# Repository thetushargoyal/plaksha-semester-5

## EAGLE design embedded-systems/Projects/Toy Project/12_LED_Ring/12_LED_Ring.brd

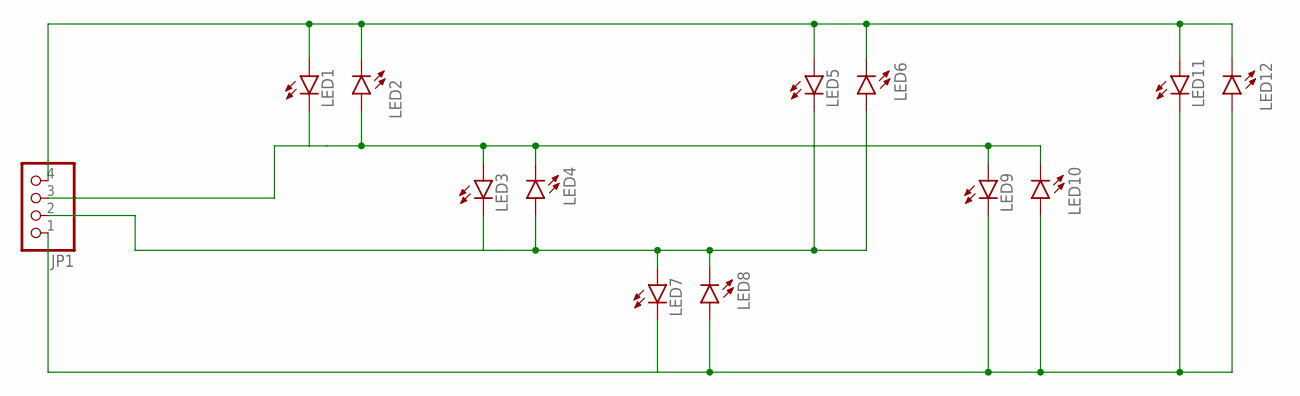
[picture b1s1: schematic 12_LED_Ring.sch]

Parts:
JP1: PINHD-1X4; 1X04
LED1, LED2, LED3, LED4, LED5, LED6, LED7, LED8, LED9, LED10, LED11, LED12: LED5MM

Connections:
unnamed: JP1.4, LED1.A, LED2.K (C), LED5.A, LED6.K (C), LED11.A, LED12.K (C)
unnamed: JP1.3, LED1.K (C), LED2.A, LED3.A, LED4.K (C), LED9.A, LED10.K (C)
unnamed: JP1.2, LED3.K (C), LED4.A, LED5.K (C), LED6.A, LED7.A, LED8.K (C)
unnamed: JP1.1, LED7.K (C), LED8.A, LED9.K (C), LED10.A, LED11.K (C), LED12.A

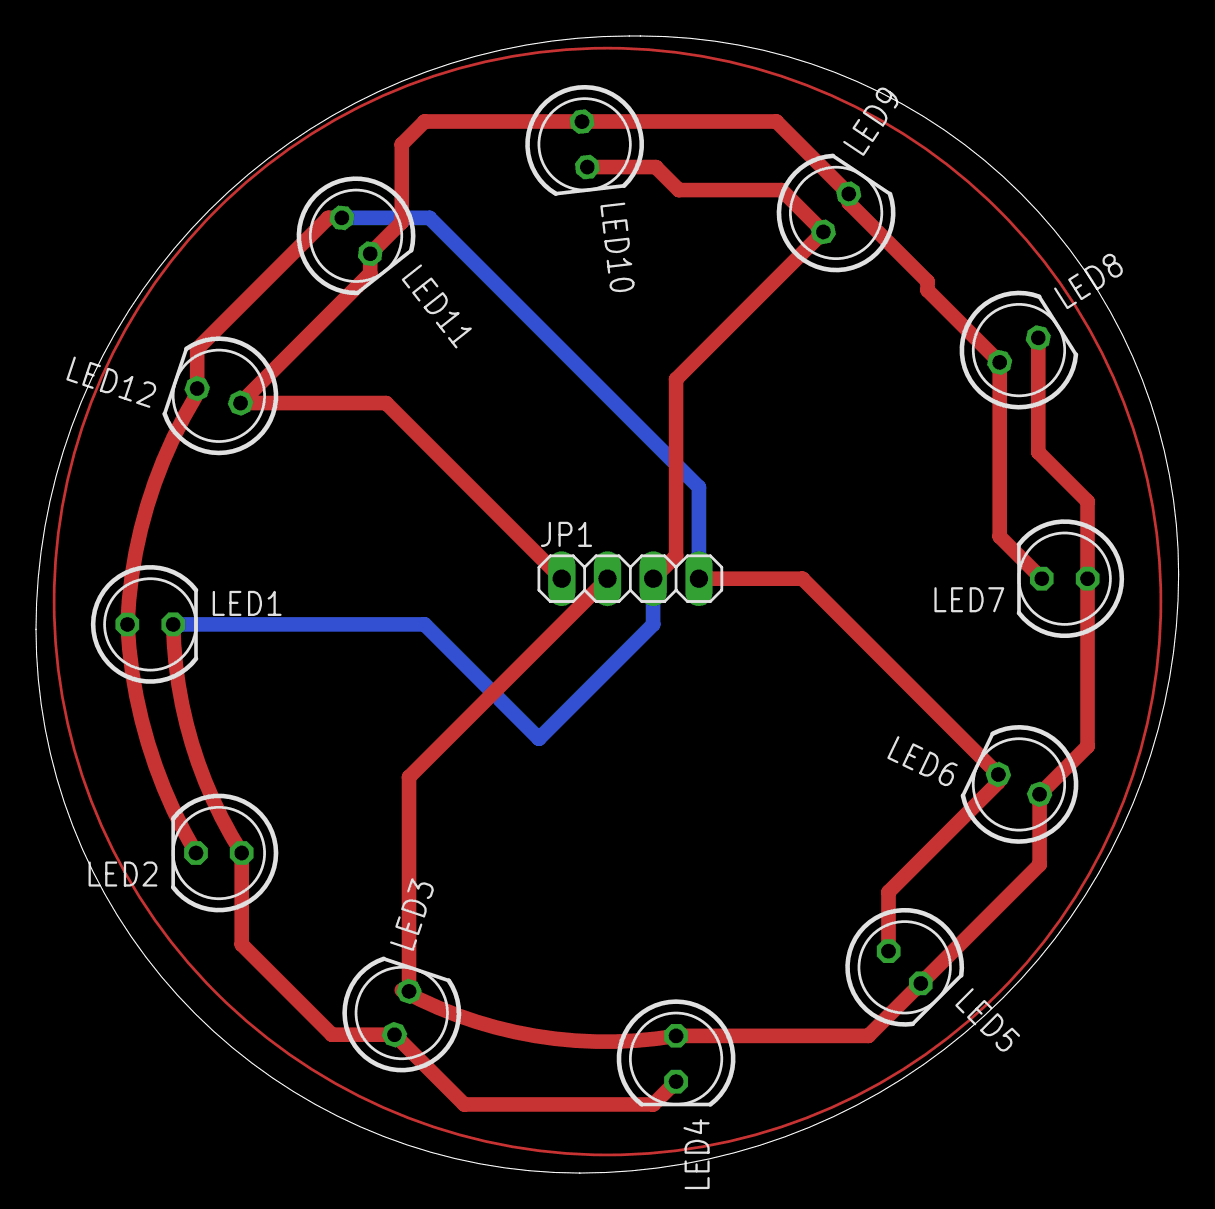
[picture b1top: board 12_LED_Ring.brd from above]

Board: 2 copper layers, 63.5 x 63.2 mm, 13 parts (0 on the bottom side), 4 nets.

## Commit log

2023-08-23 added mlpr course
2023-08-30 mlpr-lab-2-added
2023-09-24 deleted nptel lectures
